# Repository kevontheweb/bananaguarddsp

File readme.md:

# 🍌 Banana Guard DSP

I was watching adventure time, and thought it would be cool to make a PCB in the shape of one of the banana guards.

At the same time I've been meaning to do a DSP board to fiddle around with.

I know there are plenty of dev boards around that I could use, but food tastes better when you make everything from scratch 😋.

Here's a very WIP layout:

## Vision

An all-in-one DSP development platform for sonic exploration 🎤

In no particular order:

1. USB Midi (this will mostly be a FW thing I suspect)
2. Stereo audio in and out
3. _Enough_ inputs (buttons/pots)
4. Necessary analogue circuitry (so that it can realistically be used as a standalone effect/synth in a real setup)
5. Power from USB or DC jack
7. _fun_ ✨
8. A jumping-off-point dev platform for audio DSP projects (maybe with lua/faust support for DSP "blocks" or something)

## Parts choices

I went with the RP2350 from raspberry pi 🥧 because it's new and cool (🤷 at least I'm honest)
It has both an ARM and a RISC core.
I also like using the SDK much more than fighting CubeIDE (🤮).

Regarding codecs... I was initially prepared to use separate DAC/ADC's but after some cursory investigation, the consensus online seems to be that all in one codecs are usually a better choice for real time audio; since they suffer less from unsynchronised clocks, and have a lot of useful analogue front-end features.
I settled on the Texas Instruments TLV320AIC32 mainly because of a **random Reddit comment**, and the fact that Phil's Lab on YouTube used it in his guitar FX DSP board (see [Digital Audio Processing with STM32 \#1 - Introduction and Filters - Phil's Lab \#46](https://www.youtube.com/watch?v=VDhmVrbSpqA)).

## Design

I used an image from a [tutorial on how to draw the banana guard](https://easydraweverything.com/cartoon/banana-guard-adventure-time-drawing/) and then did an outline in inkscape.

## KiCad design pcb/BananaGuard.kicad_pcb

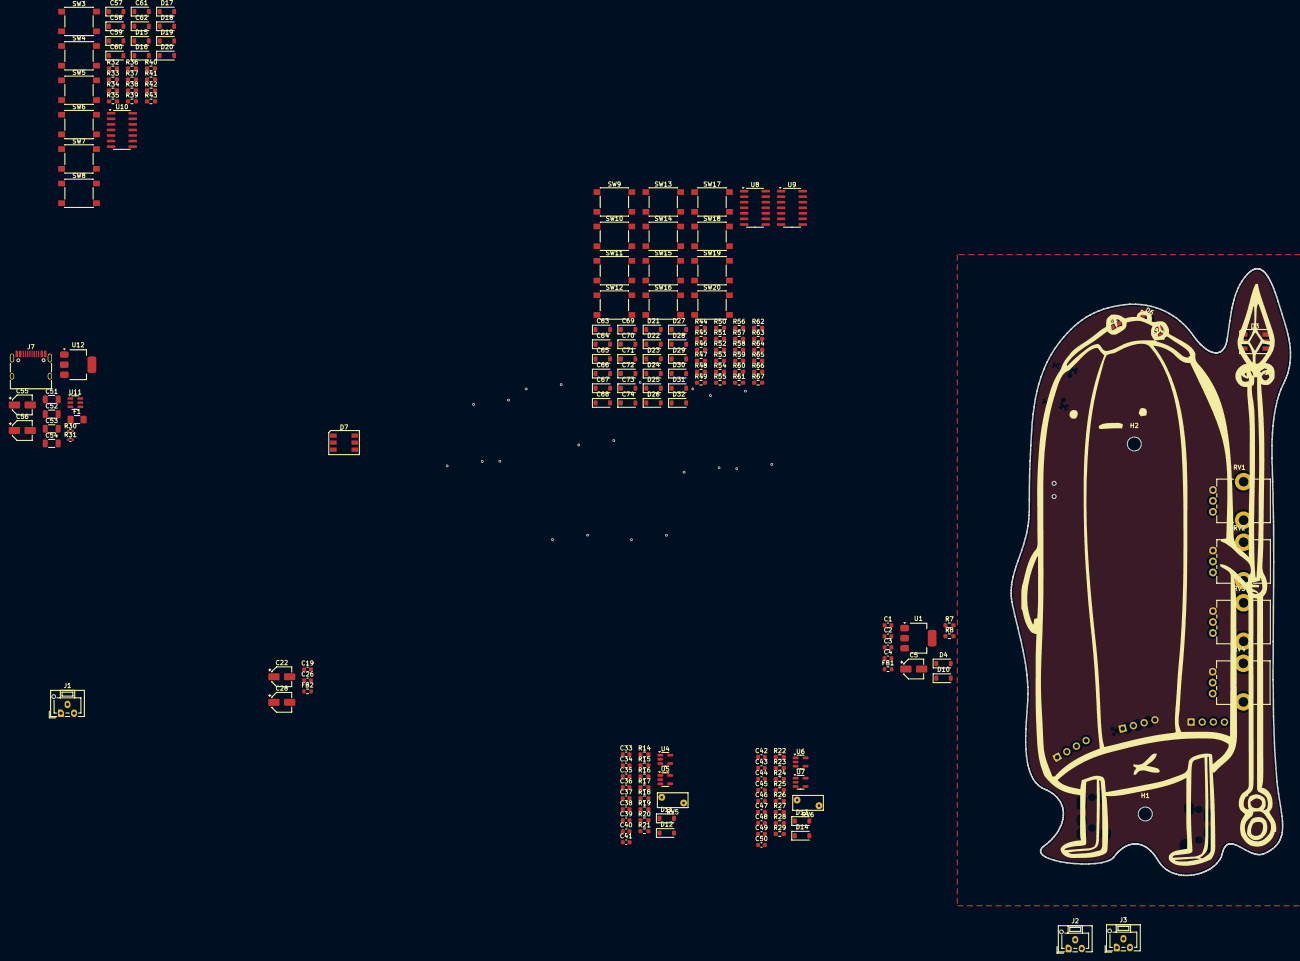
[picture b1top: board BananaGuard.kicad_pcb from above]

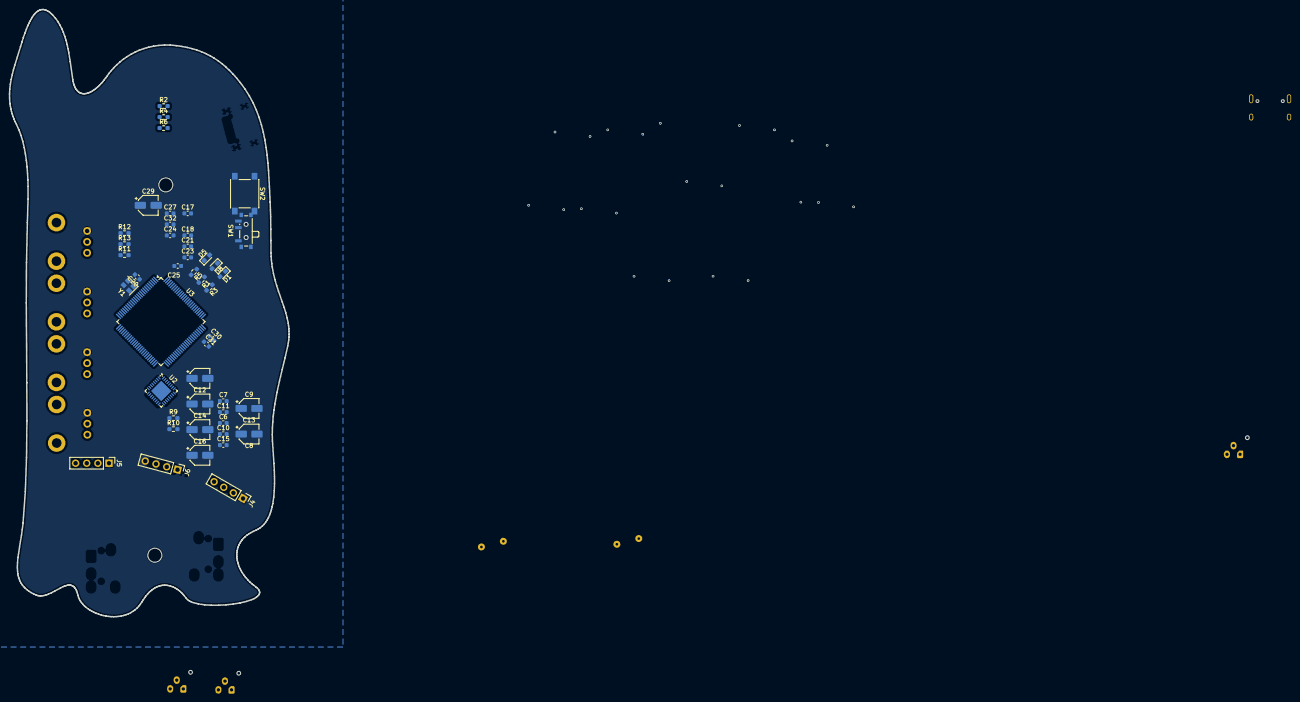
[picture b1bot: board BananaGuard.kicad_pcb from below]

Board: 4 copper layers, 63.8 x 138.6 mm, 224 parts (45 on the bottom side), 126 nets, no tracks yet.

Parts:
C1, C2, C4, C30, C31: 2.2u; C_0603_1608Metric
C3: 1u; C_0603_1608Metric
C5: 47u; CP_Elec_4x3
C6, C7, C10, C11, C15: 0.1u; C_0603_1608Metric
C8, C9, C12, C13, C16, C22, C28, C55: 1u; CP_Elec_4x3
C14, C29: 10u; CP_Elec_4x3
C17, C18, C21, C23, C25, C26, C27, C32, C36, C37, C38, C45, C46, C47: 100n; C_0603_1608Metric
C19, C34, C43: 10n; C_0603_1608Metric
C20, C24: 20p; C_0603_1608Metric
C33, C42: 220p; C_0603_1608Metric
C35, C39, C40, C41, C44, C48, C49, C50: 10u; C_0603_1608Metric
C51, C52, C53, C54: 100uF; C_1206_3216Metric
C56: 2.2u; CP_Elec_4x3
C57, C58, C59, C60, C61, C62, C63, C64, C65, C66, C67, C68, C69, C70, C71, C72, C73, C74: 2.2u; D_SOD-123
D1, D2, D5, D6, D8, D9: LED; LED_0603_1608Metric_Pad1.05x0.95mm_HandSolder
D3, D7: WS2812; LED_WS2812_PLCC6_5.0x5.0mm_P1.6mm
D4, D10, D12, D14: D_Schottky; D_SOD-123
D11, D13: CG0402MLU-12G; D_SOD-123
D15, D16, D17, D18, D19, D20, D21, D22, D23, D24, D25, D26, D27, D28, D29, D30, D31, D32: 1N4148; D_SOD-123
F1: SL1206150; Fuse_1206_3216Metric_Pad1.42x1.75mm_HandSolder
FB1, FB2: 120R; R_0603_1608Metric
H1, H2: MountingHole; MountingHole_3.2mm_M3
J1, J2, J3: Conn_01x03_Socket; JST_ZE_B03B-ZESK-1D_1x03_P1.50mm_Vertical
J4, J5, J6: Conn_01x04_Pin; PinHeader_1x04_P2.54mm_Vertical
J7: USB_C_Receptacle_USB2.0_16P; USB_C_Receptacle_HRO_TYPE-C-31-M-12
R1, R2, R3, R4, R5, R6: 270; R_0603_1608Metric_Pad0.98x0.95mm_HandSolder
R7, R8, R9, R10, R12, R17, R20, R21, R25, R28, R29: 1k; R_0603_1608Metric_Pad0.98x0.95mm_HandSolder
R11, R13: 0; R_0603_1608Metric_Pad0.98x0.95mm_HandSolder
R14, R22: 100R; R_0603_1608Metric_Pad0.98x0.95mm_HandSolder
R15, R16, R18, R23, R24, R26: 1M; R_0603_1608Metric_Pad0.98x0.95mm_HandSolder
R19, R27: 100; R_0603_1608Metric_Pad0.98x0.95mm_HandSolder
R30, R31: 5.1k; R_0402_1005Metric
R32, R34, R36, R38, R40, R42, R44, R46, R48, R50, R52, R54, R56, R58, R60, R62, R64, R66: 2.26k 1%; R_0603_1608Metric_Pad0.98x0.95mm_HandSolder
R33, R35, R37, R39, R41, R43, R45, R47, R49, R51, R53, R55, R57, R59, R61, R63, R65, R67: 2.05k 1%; R_0603_1608Metric_Pad0.98x0.95mm_HandSolder
RV1, RV2, RV3, RV4: 10k; Potentiometer_Bourns_PTV09A-1_Single_Vertical
RV5, RV6: 12V; RV_Disc_D7mm_W3.4mm_P5mm
SW1: SW_Push_SPDT; SW_SPDT_PCM12
SW2, SW3, SW4, SW5, SW6, SW7, SW8, SW9, SW10, SW11, SW12, SW13, SW14, SW15, SW16, SW17, SW18, SW19, SW20: SW_Push; SW_SPST_PTS645
U1: TLV76150DCY; SOT-223-3_TabPin2
U2: TLV320AIC32IRHBR; QFN-32-1EP_5x5mm_P0.5mm_EP3.3x3.3mm
U3: STM32F429VITx; LQFP-100_14x14mm_P0.5mm
U4, U5, U6, U7: TLV9061xDBV; SOT-23-5
U8, U9, U10: 74HC14; SO-14_3.9x8.65mm_P1.27mm
U11: USBLC6-2SC6; SOT-23-6
U12: TLV76133DCY; SOT-223-3_TabPin2
Y1: 25 MHz; Crystal_SMD_2520-4Pin_2.5x2.0mm

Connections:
+1.8V: C7.1, C9.1, U2.32 (DVDD)
+2.5V: C5.1, R7.1, R8.2, R15.2, R18.2, R23.2, R26.2
+3.3V: C11.1, C13.1, C17.1, C18.1, C19.1, C21.1, C22.1, C23.1, C25.1, C27.1, C29.1, C56.1, D3.3 (VCC), D7.3 (VCC), FB2.1, J4.4, J5.4, J6.4, R9.1, R10.1, RV1.1, RV2.1, RV3.1, RV4.1, SW1.3 (C), U2.7 (IOVDD), U3.11 (VDD), U3.19 (VDD), U3.28 (VDD), U3.50 (VDD), U3.75 (VDD), U3.100 (VDD), U12.2 (VO)
+3.3VA: C6.1, C8.1, C10.1, C12.1, C14.1, C15.1, C16.1, C26.1, C28.1, FB2.2, R13.1, U2.18 (DRVDD), U2.24 (DRVDD), U2.25 (AVDD), U3.22 (VDDA)
+5V: C4.1, C37.1, C38.1, C46.1, C47.1, R7.2, U1.2 (VO), U4.5 (V+), U5.5 (V+), U6.5 (V+), U7.5 (V+)
/A: U3.40 (PE9), U8.12
/A#: U3.41 (PE10), U9.12
/AUDIO_INPUT_L: D11.1 (K), J2.3, R14.1, RV5.1
/AUDIO_INPUT_R: D13.1 (K), J2.1, R22.1, RV6.1
/B: U3.42 (PE11), U9.2
/BUFFERED_AUDIO_INPUT_L: C41.2, U2.10 (MIC1L/LINE1L)
/BUFFERED_AUDIO_INPUT_R: C50.2, U2.11 (MIC1R/LINE1R)
/BUFFERED_AUDIO_OUTPUT_L: C39.2, D12.1 (K), J3.1, R21.2
/BUFFERED_AUDIO_OUTPUT_R: C48.2, D14.1 (K), J3.3, R29.2
/Buttons/Debounced Button/OUT_TO_SCHMIDT_TRIGGER: C62.1, D20.1 (K), R43.2, U10.1
/C: U3.97 (PE0), U8.2
/C#: U3.98 (PE1), U8.4
/CODEC_AUDIO_OUTPUT_L: C34.1, U2.27 (LEFT_LOP)
/CODEC_AUDIO_OUTPUT_R: C43.1, U2.29 (RIGHT_LOP)
/D: U3.1 (PE2), U9.4
/D#: U3.2 (PE3), U8.6
/DEBUG_LED1: R1.1, U3.32 (PA7)
/DEBUG_LED2: R3.1, U3.67 (PA8)
/DEBUG_LED3: R5.1, U3.77 (PA15)
/DOWN: U3.86 (PD5), U10.12
/E: U3.3 (PE4), U9.6
/F: U3.4 (PE5), U8.8
/F#: U3.5 (PE6), U9.8
/G: U3.38 (PE7), U8.10
/G#: U3.39 (PE8), U9.10
/HAT_LED1: R2.1, U3.35 (PB0)
/HAT_LED2: R4.1, U3.36 (PB1)
/HAT_LED3: R6.1, U3.37 (PB2)
/I2S_BCK: U2.2 (BCLK), U3.47 (PB10)
/I2S_MCK: U2.1 (MCLK), U3.63 (PC6)
/I2S_SD_ADC: U2.5 (DOUT), U3.18 (PC3)
/I2S_SD_DAC: U2.4 (DIN), U3.17 (PC2)
/I2S_WS: U2.3 (WCLK), U3.51 (PB12)
/Keys/Debounced Button1/OUT_TO_SCHMIDT_TRIGGER: C65.1, D23.1 (K), R49.2, U9.3
/Keys/Debounced Button2/OUT_TO_SCHMIDT_TRIGGER: C67.1, D25.1 (K), R53.2, U9.5
/Keys/Debounced Button3/OUT_TO_SCHMIDT_TRIGGER: C68.1, D26.1 (K), R55.2, U8.9
/Keys/Debounced Button4/OUT_TO_SCHMIDT_TRIGGER: C70.1, D28.1 (K), R59.2, U8.11
/Keys/Debounced Button5/OUT_TO_SCHMIDT_TRIGGER: C72.1, D30.1 (K), R63.2, U8.13
/Keys/Debounced Button6/OUT_TO_SCHMIDT_TRIGGER: C74.1, D32.1 (K), R67.2, U9.1
/Keys/Debounced Button7/OUT_TO_SCHMIDT_TRIGGER: C64.1, D22.1 (K), R47.2, U8.3
/Keys/Debounced Button8/OUT_TO_SCHMIDT_TRIGGER: C66.1, D24.1 (K), R51.2, U8.5
/Keys/Debounced Button9/OUT_TO_SCHMIDT_TRIGGER: C69.1, D27.1 (K), R57.2, U9.9
/Keys/Debounced Button10/OUT_TO_SCHMIDT_TRIGGER: C71.1, D29.1 (K), R61.2, U9.11
/Keys/Debounced Button11/OUT_TO_SCHMIDT_TRIGGER: C73.1, D31.1 (K), R65.2, U9.13
/Keys/Debounced Button/OUT_TO_SCHMIDT_TRIGGER: C63.1, D21.1 (K), R45.2, U8.1
/LED_DIN: D3.2 (DIN), U3.31 (PA6)
/LEFT: U3.83 (PD2), U10.6
/OCTAVE_DOWN: U3.82 (PD1), U10.4
/OCTAVE_UP: U3.81 (PD0), U10.2
/POT1: RV1.2, U3.23 (PA0)
/POT2: RV2.2, U3.24 (PA1)
/POT3: RV3.2, U3.25 (PA2)
/POT4: RV4.2, U3.26 (PA3)
/RIGHT: U3.84 (PD3), U10.8
/SCL: J5.3, R9.2, U2.8 (SCL), U3.93 (PB7)
/SDA: J5.2, R10.2, U2.9 (SDA), U3.92 (PB6)
/STM32F429VIT6/RESET: C32.1, SW2.2, U3.14 (NRST)
/STM32F429VIT6/SWCLCK: J6.2, U3.76 (PA14)
/STM32F429VIT6/SWDIO: J6.3, U3.72 (PA13)
/STM32F429VIT6/XTAL_IN: R11.1, U3.12 (PH0)
/STM32F429VIT6/XTAL_OUT: C24.1, U3.13 (PH1), Y1.4
/UART_RX: J4.2, U3.69 (PA10)
/UART_TX: J4.3, U3.68 (PA9)
/UP: U3.85 (PD4), U10.10
/USB/D+: J7.A6 (D+), J7.B6 (D+), U11.3 (I/O2)
/USB/D-: J7.A7 (D-), J7.B7 (D-), U11.1 (I/O1)
/USB/V_{BUS_IN}: F1.1, J7.A4 (VBUS), J7.A9 (VBUS), J7.B4 (VBUS), J7.B9 (VBUS)
/USB_D+: U3.71 (PA12), U11.4 (I/O2)
/USB_D-: U3.70 (PA11), U11.6 (I/O1)
/~CODEC_RESET: U2.31 (~RESET), U3.89 (PB3)
GND: C1.2, C2.2, C3.2, C4.2, C6.2, C7.2, C8.2, C9.2, C10.2, C11.2, C12.2, C13.2, C14.2, C15.2, C16.2, C17.2, C18.2, C19.2, C20.2, C21.2, C22.2, C23.2, C24.2, C25.2, C26.2, C27.2, C28.2, C29.2, C30.2, C31.2, C32.2, C36.1, C37.2, C38.2, C40.1, C45.1, C46.2, C47.2, C49.1, C51.2, C52.2, C53.2, C54.2, C55.2, C56.2, C62.2, C63.2, C64.2, C65.2, C66.2, C67.2, C68.2, C69.2, C70.2, C71.2, C72.2, C73.2, C74.2, D1.1 (K), D2.1 (K), D3.6 (VSS), D4.2 (A), D5.1 (K), D6.1 (K), D7.6 (VSS), D8.1 (K), D9.1 (K), D12.2 (A), D14.2 (A), J1.1, J2.2, J3.2, J4.1, J5.1, J6.1, J7.A1 (GND), J7.A12 (GND), J7.B1 (GND), J7.B12 (GND), J7.S1 (SHIELD), R21.1, R29.1, R30.2, R31.2, RV1.3, RV2.3, RV3.3, RV4.3, SW1.1 (A), SW2.1, SW8.2, SW9.2, SW10.2, SW11.2, SW12.2, SW13.2, SW14.2, SW15.2, SW16.2, SW17.2, SW18.2, SW19.2, SW20.2, U1.1 (GND), U2.6 (DVSS), U2.17 (AVSS1), U2.21 (DRVSS), U2.26 (AVSS2), U2.33 (EPAD), U3.10 (VSS), U3.20 (VSSA), U3.27 (VSS), U3.74 (VSS), U3.99 (VSS), U4.2 (V-), U5.2 (V-), U6.2 (V-), U7.2 (V-), U8.7 (GND), U9.7 (GND), U10.7 (GND), U11.2 (GND), U12.1 (GND), Y1.2, Y1.3
unnamed: C5.2, R8.1
unnamed: C20.1, R11.2, Y1.1
unnamed: C33.1, C35.1, R14.2, R16.2
unnamed: C34.2, R15.1, R17.2
unnamed: C39.1, R19.2
unnamed: C40.2, C41.1, R20.2
unnamed: C42.1, C44.1, R22.2, R24.2
unnamed: C43.2, R23.1, R25.2
unnamed: C48.1, R27.2
unnamed: C49.2, C50.1, R28.2
unnamed: D1.2 (A), R1.2
unnamed: D2.2 (A), R2.2
unnamed: D3.1 (DOUT), D7.2 (DIN)
unnamed: D5.2 (A), R3.2
unnamed: D6.2 (A), R4.2
unnamed: D8.2 (A), R5.2
unnamed: D9.2 (A), R6.2
unnamed: C2.1, C3.1, D10.1 (K), FB1.2, U1.3 (VI)
unnamed: C33.2, D11.2 (A), R16.1, RV5.2
unnamed: C42.2, D13.2 (A), R24.1, RV6.2
unnamed: D20.2 (A), R42.2, R43.1, SW8.1
unnamed: D21.2 (A), R44.2, R45.1, SW9.1
unnamed: D22.2 (A), R46.2, R47.1, SW10.1
unnamed: D23.2 (A), R48.2, R49.1, SW11.1
unnamed: D24.2 (A), R50.2, R51.1, SW12.1
unnamed: D25.2 (A), R52.2, R53.1, SW13.1
unnamed: D26.2 (A), R54.2, R55.1, SW14.1
unnamed: D27.2 (A), R56.2, R57.1, SW15.1
unnamed: D28.2 (A), R58.2, R59.1, SW16.1
unnamed: D29.2 (A), R60.2, R61.1, SW17.1
unnamed: D30.2 (A), R62.2, R63.1, SW18.1
unnamed: D31.2 (A), R64.2, R65.1, SW19.1
unnamed: D32.2 (A), R66.2, R67.1, SW20.1
unnamed: J7.A5 (CC1), R30.1
unnamed: J7.B5 (CC2), R31.1
unnamed: R12.1, SW1.2 (B)
unnamed: R12.2, U3.94 (BOOT0)
unnamed: C30.1, U3.49 (VCAP_1)
unnamed: C31.1, U3.73 (VCAP_2)
unnamed: R13.2, U3.21 (VREF+)
unnamed: C36.2, R17.1, U4.3 (+)
unnamed: R19.1, U4.1, U4.4 (-)
unnamed: C35.2, R18.1, U5.3 (+)
unnamed: R20.1, U5.1, U5.4 (-)
unnamed: C45.2, R25.1, U6.3 (+)
unnamed: R27.1, U6.1, U6.4 (-)
unnamed: C44.2, R26.1, U7.3 (+)
unnamed: R28.1, U7.1, U7.4 (-)
VBUS: C51.1, C52.1, C53.1, C54.1, C55.1, D3.5 (VDD), D7.5 (VDD), D10.2 (A), F1.2, U11.5 (VBUS), U12.3 (VI)
VCC: C1.1, D4.1 (K), FB1.1, J1.3, R42.1, R44.1, R46.1, R48.1, R50.1, R52.1, R54.1, R56.1, R58.1, R60.1, R62.1, R64.1, R66.1, U8.14 (VCC), U9.14 (VCC), U10.14 (VCC)

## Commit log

2025-02-22 🍌 new project, who dis?
2025-02-22 🐒 spell banana correctly...
2025-02-23 ⚙️ wip, stm32 reference schem + jobset
2025-02-23 more readme info
2025-02-24 🎛 wip analogue front end
2025-03-01 analogue fe + buttons/keys
2025-03-01 more schematic stuff, preliminary footprint choices and parts grouping, played with multicahnnel for the buttons
2025-03-03 expand usb, piano keys, cleanup
2025-03-21 switch back to rp2350, ideal diode OR'ing for power
2025-03-21 🌈 update readme
